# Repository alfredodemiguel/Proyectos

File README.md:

Recopilación de proyectos que realizo, por mero divertimento.
Este repositorio alberga proyectos, de dispositivos, con todo su software asociado y otros que son simples aplicaciones en Java o app moviles en React Native.

Dentro de cada proyecto hay una descripción mas detallada, de su función.

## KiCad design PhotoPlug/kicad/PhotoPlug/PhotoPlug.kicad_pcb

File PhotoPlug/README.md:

El proyecto consiste en la fabricación de un artefacto, que permite tomar fotografiás, y controlar una salida de luz.

De esta forma, podemos ver remotamente como se está desarrollando una impresión 3D, y si es necesario quitar la alimentación a la impresora.

El artefacto se puede controlar desde una red wifi propia, (que también se usa para la configuración inicial), o desde una web alojada en un servidor que está en un contenedor Docker alojado en Heroku, al igueal que un servidor API-REST.

El proyecto está separado por carpetas: el diseño de la placa base, el diseño de la caja para imprimir en 3D, la programación de la ESP32-CAM, la programación de la web, la programación del servidor API-REST, y la programación de la app movil android.

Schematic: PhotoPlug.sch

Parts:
C1, C2: CP1_Small; CP_Radial_D6.3mm_P2.50mm
F1, F2: Fuse; MiFusible
H1, H2, H3, H4: MountingHole; MountingHole_3.5mm
IC1: ESP32-CAM; ESP32CAM; Manufacturer_Part_Number ESP32-CAM
J1, J5: Screw_Terminal_01x02; Altech_AK300_1x02_P5.00mm_45-Degree
J2: Screw_Terminal_01x03; Altech_AK300_1x03_P5.00mm_45-Degree
J3: Screw_Terminal_01x02; Altech_AK300_1x03_P5.00mm_45-Degree
J4: Conn_01x08_MountingPin; PinSocket_1x08_P1.00mm_Vertical_SMD_Pin1Left
J6, J7, J8: Conn_01x02_MountingPin; PinHeader_1x02_P1.00mm_Vertical
K1: SRD-05VDC-SL-C; SRD; Manufacturer_Part_Number SRD-05VDC-SL-C
R1, R2, R3: R; R_Axial_DIN0204_L3.6mm_D1.6mm_P2.54mm_Vertical
RV1: Varistor; RV_Disc_D12mm_W4.8mm_P7.5mm
U1: Transformador100v-240v_5V_0.6A; Transformador Tenstar Robot

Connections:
+1V5: C1.1, C2.1, F2.1
+5V: IC1.8 (5V), J4.4, J4.5
GND: C1.2, C2.2, IC1.16 (GND_3), J4.1, J4.2, J4.3, J6.1, J7.1, J8.1, K1.3, U1.3
unnamed: F1.1, J2.2
unnamed: F1.2, K1.1, RV1.2, U1.0
unnamed: F2.2, U1.2
unnamed: IC1.1 (IO4), J4.6
unnamed: IC1.2 (IO2), J4.7
unnamed: IC1.3 (IO14), J4.8
unnamed: IC1.4 (IO15), R1.2, R2.2, R3.2
unnamed: IC1.6 (IO12), K1.2
unnamed: J1.1, J2.3, J3.2
unnamed: J1.2, J3.1, J5.1, RV1.1, U1.1
unnamed: J2.1, J5.2, K1.4
unnamed: J6.2, R3.1
unnamed: J7.2, R1.1
unnamed: J8.2, R2.1

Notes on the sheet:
Interruptor de tres posiciones
Entrada
Salida
PhotoPlug
Led_Encendido

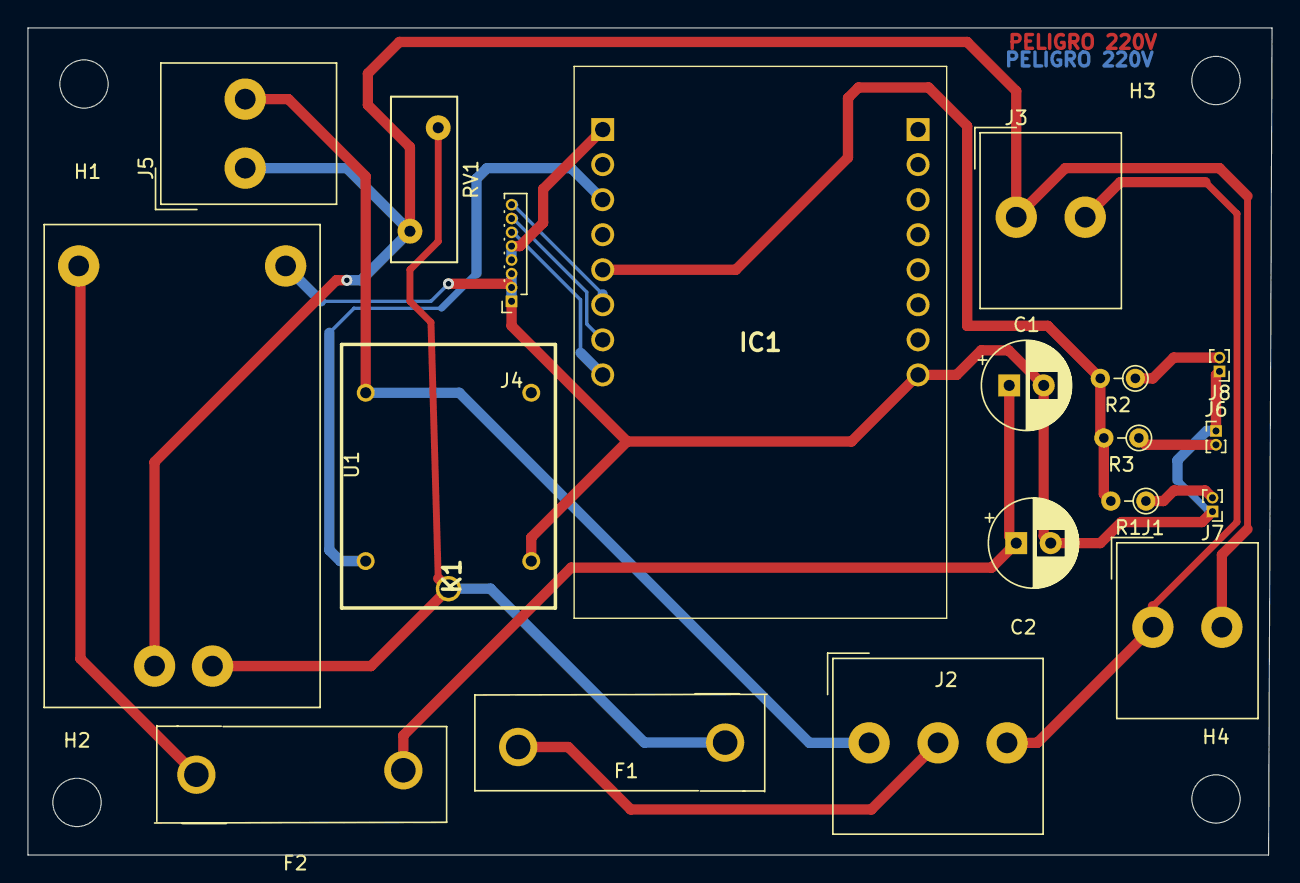
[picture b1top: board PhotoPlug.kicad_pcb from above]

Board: 2 copper layers, 90.2 x 59.9 mm, 23 parts (0 on the bottom side), 17 nets.

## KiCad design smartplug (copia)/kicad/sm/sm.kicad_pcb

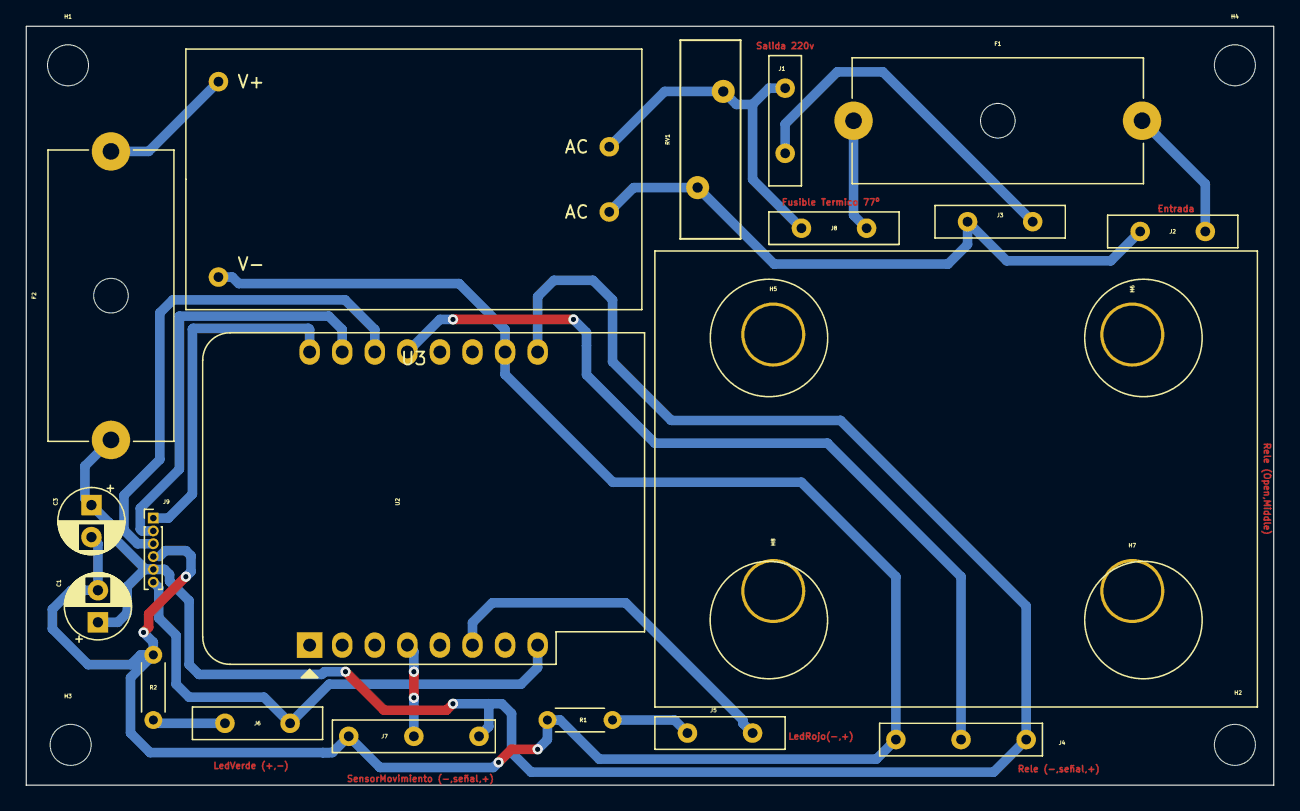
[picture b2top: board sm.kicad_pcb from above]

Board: 2 copper layers, 97.3 x 59.2 mm, 27 parts (0 on the bottom side), 17 nets.

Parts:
C1: Capacitor 22uF; CP_Radial_D5.0mm_P2.50mm
C3: Capacitor 10uF; CP_Radial_D5.0mm_P2.50mm
F1: Portafusible para fusible 5x20mm (Slow Blow 200mA); Fuseholder_Cylinder-5x20mm_Schurter_0031_8201_Horizontal_Op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
F2: Portafusible para fusible 5x20mm (Quick Blow 630m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; Fuseholder_Cylinder-5x20mm_Schurter_0031_8201_Horizontal_Op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
H1, H2, H3, H4, H5, H6, H7, H8: MountingHole; MountingHole_3.2mm_M3_DIN965
J1, J2, J3, J5, J6, J8: Screw_Terminal_01x02; Terminal_Tornillo_2
J4, J7: Screw_Terminal_01x03; Terminal_Tornillo_3
J9: Conn_01x06_Male; PinHeader_1x06_P1.00mm_Vertical
R1, R2: Resistencia 200 ohms; R_Axial_DIN0204_L3.6mm_D1.6mm_P5.08mm_Horizontal
RV1: Varistor 300 v 14d471k; RV_Disc_D15.5mm_W4.7mm_P7.5mm
U1: RELE QC3F-05VDC (10A 125-220 - 10A 30VDC); Rele_5vDC
U2: ESP8266 ESP-12F; ESP8266_ESP-12F3
U3: Transformador100v-240v_5V_0.6A; Transformador220v-5v

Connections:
+3V3: J6.1, J9.6, U2.8
+5V: C1.1, C3.1, F2.1, J4.3, J7.3, J9.5, U2.16
/Linea1: F1.2, J2.1
/Linea2: J2.2, J3.2, RV1.2, U3.1
GND: C1.2, C3.2, J4.1, J7.1, J9.4, R1.2, R2.2, U2.15, U3.2
unnamed: F1.1, J8.2
unnamed: F2.2, U3.3
unnamed: J1.1, J8.1, RV1.1, U3.0
unnamed: J1.2, J3.1
unnamed: J4.2, U2.12
unnamed: J5.1, U2.6
unnamed: J5.2, R1.1
unnamed: J6.2, R2.1
unnamed: J7.2, U2.4
unnamed: J9.1, U2.9
unnamed: J9.2, U2.10
unnamed: J9.3, U2.11

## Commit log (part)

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2020-03-04 organizacion
2020-03-22 Linux
2020-03-30 callbacks
2020-04-02 cambio pag
2020-04-03 Optimizar api
2020-04-11 API ok
2020-05-03 freecad
2020-05-06 Placa mas pequeña
2020-05-18 web arduino
2020-05-26 email
2020-05-30 Antes refactorizar
2020-06-04 Antes email
2020-06-17 Finalizando arduino
2020-06-21 Programa arduino
2020-07-05 Paso array
2020-07-10 web a medias
2020-07-11 web funcionando
2020-07-19 Bump lodash from 4.17.15 to 4.17.19 in /smartplug/system
    Bumps [lodash](https://github.com/lodash/lodash) from 4.17.15 to 4.17.19.
    - [Release notes](https://github.com/lodash/lodash/releases)
    - [Commits](https://github.com/lodash/lodash/compare/4.17.15...4.17.19)
2020-07-21 Web 1.0
2020-09-08 Integración con get
2020-09-15 FotoString
2020-10-11 fusion
2020-10-17 Paso a SD
2020-10-25 Comportamiento
2020-10-26 Hardware y web
2021-01-02 CajaLimpia
2021-01-05 Arduino revisado
2021-01-10 Bump dot-prop from 4.2.0 to 4.2.1 in /PhotoPlug/system
    Bumps [dot-prop](https://github.com/sindresorhus/dot-prop) from 4.2.0 to 4.2.1.
    - [Release notes](https://github.com/sindresorhus/dot-prop/releases)
    - [Commits](https://github.com/sindresorhus/dot-prop/compare/v4.2.0...v4.2.1)
2021-01-10 Bump ini from 1.3.5 to 1.3.8 in /PhotoPlug/system
    Bumps [ini](https://github.com/isaacs/ini) from 1.3.5 to 1.3.8.
    - [Release notes](https://github.com/isaacs/ini/releases)
    - [Commits](https://github.com/isaacs/ini/compare/v1.3.5...v1.3.8)
2021-01-19 AntesRefactorinWeb
2021-01-22 Bump dot-prop from 4.2.0 to 4.2.1 in /PhotoPlug/API
    Bumps [dot-prop](https://github.com/sindresorhus/dot-prop) from 4.2.0 to 4.2.1.
    - [Release notes](https://github.com/sindresorhus/dot-prop/releases)
    - [Commits](https://github.com/sindresorhus/dot-prop/compare/v4.2.0...v4.2.1)
2021-01-22 Bump lodash from 4.17.15 to 4.17.20 in /PhotoPlug/API
    Bumps [lodash](https://github.com/lodash/lodash) from 4.17.15 to 4.17.20.
    - [Release notes](https://github.com/lodash/lodash/releases)
    - [Commits](https://github.com/lodash/lodash/compare/4.17.15...4.17.20)
2021-01-22 Bump ini from 1.3.5 to 1.3.8 in /smartplug/system
    Bumps [ini](https://github.com/isaacs/ini) from 1.3.5 to 1.3.8.
    - [Release notes](https://github.com/isaacs/ini/releases)
    - [Commits](https://github.com/isaacs/ini/compare/v1.3.5...v1.3.8)
2021-01-22 Bump ini from 1.3.5 to 1.3.8 in /PhotoPlug/API
    Bumps [ini](https://github.com/isaacs/ini) from 1.3.5 to 1.3.8.
    - [Release notes](https://github.com/isaacs/ini/releases)
    - [Commits](https://github.com/isaacs/ini/compare/v1.3.5...v1.3.8)
2021-01-22 Bump axios from 0.19.2 to 0.21.1 in /PhotoPlug/webCamera/web
    Bumps [axios](https://github.com/axios/axios) from 0.19.2 to 0.21.1.
    - [Release notes](https://github.com/axios/axios/releases)
    - [Changelog](https://github.com/axios/axios/blob/v0.21.1/CHANGELOG.md)
    - [Commits](https://github.com/axios/axios/compare/v0.19.2...v0.21.1)
2021-01-24 PhotoPlug
2021-02-06 Botones app movil
2021-03-22 imagenes
2021-04-09 versionNode
2021-04-11 media web
2021-05-08 Bump ua-parser-js from 0.7.23 to 0.7.28 in /PhotoPlug/AppMovil/PhotoPlug
    Bumps [ua-parser-js](https://github.com/faisalman/ua-parser-js) from 0.7.23 to 0.7.28.
    - [Release notes](https://github.com/faisalman/ua-parser-js/releases)
    - [Commits](https://github.com/faisalman/ua-parser-js/compare/0.7.23...0.7.28)
2021-05-11 Bump hosted-git-info in /PhotoPlug/AppMovil/PhotoPlug
    Bumps [hosted-git-info](https://github.com/npm/hosted-git-info) from 2.8.8 to 2.8.9.
    - [Release notes](https://github.com/npm/hosted-git-info/releases)
    - [Changelog](https://github.com/npm/hosted-git-info/blob/v2.8.9/CHANGELOG.md)
    - [Commits](https://github.com/npm/hosted-git-info/compare/v2.8.8...v2.8.9)
2021-05-12 Bump lodash from 4.17.15 to 4.17.21 in /PhotoPlug/API
    Bumps [lodash](https://github.com/lodash/lodash) from 4.17.15 to 4.17.21.
    - [Release notes](https://github.com/lodash/lodash/releases)
    - [Commits](https://github.com/lodash/lodash/compare/4.17.15...4.17.21)
2021-06-12 Bump glob-parent from 5.1.1 to 5.1.2 in /PhotoPlug/AppMovil/PhotoPlug
    Bumps [glob-parent](https://github.com/gulpjs/glob-parent) from 5.1.1 to 5.1.2.
    - [Release notes](https://github.com/gulpjs/glob-parent/releases)
    - [Changelog](https://github.com/gulpjs/glob-parent/blob/main/CHANGELOG.md)
    - [Commits](https://github.com/gulpjs/glob-parent/compare/v5.1.1...v5.1.2)
    ---
    updated-dependencies:
2021-07-09 get funcionando
2021-07-17 antes try catch
2021-07-19 API sin test
2021-07-31 Test Inicio
2021-08-13 Bump path-parse from 1.0.6 to 1.0.7 in /PhotoPlug/AppMovil/PhotoPlug
    Bumps [path-parse](https://github.com/jbgutierrez/path-parse) from 1.0.6 to 1.0.7.
    - [Release notes](https://github.com/jbgutierrez/path-parse/releases)
    - [Commits](https://github.com/jbgutierrez/path-parse/commits/v1.0.7)
    ---
    updated-dependencies:
    - dependency-name: path-parse
2022-02-11 Bump pathval from 1.1.0 to 1.1.1 in /PhotoPlug/API
    Bumps [pathval](https://github.com/chaijs/pathval) from 1.1.0 to 1.1.1.
    - [Release notes](https://github.com/chaijs/pathval/releases)
    - [Changelog](https://github.com/chaijs/pathval/blob/master/CHANGELOG.md)
    - [Commits](https://github.com/chaijs/pathval/compare/v1.1.0...v1.1.1)
    ---
    updated-dependencies:
2022-02-14 Bump follow-redirects from 1.14.1 to 1.14.8 in /ApiSql
    Bumps [follow-redirects](https://github.com/follow-redirects/follow-redirects) from 1.14.1 to 1.14.8.
    - [Release notes](https://github.com/follow-redirects/follow-redirects/releases)
    - [Commits](https://github.com/follow-redirects/follow-redirects/compare/v1.14.1...v1.14.8)
    ---
    updated-dependencies:
    - dependency-name: follow-redirects
2022-03-29 Bump minimist from 1.2.5 to 1.2.6 in /PhotoPlug/AppMovil/PhotoPlug
    Bumps [minimist](https://github.com/substack/minimist) from 1.2.5 to 1.2.6.
    - [Release notes](https://github.com/substack/minimist/releases)
    - [Commits](https://github.com/substack/minimist/compare/1.2.5...1.2.6)
    ---
    updated-dependencies:
    - dependency-name: minimist
2022-03-30 Bump minimist from 1.2.5 to 1.2.6 in /ApiSql
    Bumps [minimist](https://github.com/substack/minimist) from 1.2.5 to 1.2.6.
    - [Release notes](https://github.com/substack/minimist/releases)
    - [Commits](https://github.com/substack/minimist/compare/1.2.5...1.2.6)
    ---
    updated-dependencies:
    - dependency-name: minimist
2022-06-02 Bump simple-plist from 1.1.1 to 1.3.1 in /PhotoPlug/AppMovil/PhotoPlug
    Bumps [simple-plist](https://github.com/wollardj/simple-plist) from 1.1.1 to 1.3.1.
    - [Release notes](https://github.com/wollardj/simple-plist/releases)
    - [Commits](https://github.com/wollardj/simple-plist/compare/v1.1.1...v1.3.1)
    ---
    updated-dependencies:
    - dependency-name: simple-plist
2022-06-22 Bump async from 3.2.0 to 3.2.4 in /ApiSql
    Bumps [async](https://github.com/caolan/async) from 3.2.0 to 3.2.4.
    - [Release notes](https://github.com/caolan/async/releases)
    - [Changelog](https://github.com/caolan/async/blob/master/CHANGELOG.md)
    - [Commits](https://github.com/caolan/async/compare/v3.2.0...v3.2.4)
    ---
    updated-dependencies:
2022-11-10 Bump minimatch and mocha in /PhotoPlug/API
    Bumps [minimatch](https://github.com/isaacs/minimatch) to 3.1.2 and updates ancestor dependency [mocha](https://github.com/mochajs/mocha). These dependencies need to be updated together.
    Updates `minimatch` from 3.0.4 to 3.1.2
    - [Release notes](https://github.com/isaacs/minimatch/releases)
    - [Commits](https://github.com/isaacs/minimatch/compare/v3.0.4...v3.1.2)
    Updates `mocha` from 6.2.2 to 10.1.0
    - [Release notes](https://github.com/mochajs/mocha/releases)
2022-11-10 Bump minimatch from 3.0.4 to 3.1.2 in /PhotoPlug/AppMovil/PhotoPlug
    Bumps [minimatch](https://github.com/isaacs/minimatch) from 3.0.4 to 3.1.2.
    - [Release notes](https://github.com/isaacs/minimatch/releases)
    - [Commits](https://github.com/isaacs/minimatch/compare/v3.0.4...v3.1.2)
    ---
    updated-dependencies:
    - dependency-name: minimatch
2022-12-07 Bump decode-uri-component from 0.2.0 to 0.2.2 in /PhotoPlug/API
    Bumps [decode-uri-component](https://github.com/SamVerschueren/decode-uri-component) from 0.2.0 to 0.2.2.
    - [Release notes](https://github.com/SamVerschueren/decode-uri-component/releases)
    - [Commits](https://github.com/SamVerschueren/decode-uri-component/compare/v0.2.0...v0.2.2)
    ---
    updated-dependencies:
    - dependency-name: decode-uri-component
2022-12-07 Bump decode-uri-component in /PhotoPlug/AppMovil/PhotoPlug
    Bumps [decode-uri-component](https://github.com/SamVerschueren/decode-uri-component) from 0.2.0 to 0.2.2.
    - [Release notes](https://github.com/SamVerschueren/decode-uri-component/releases)
    - [Commits](https://github.com/SamVerschueren/decode-uri-component/compare/v0.2.0...v0.2.2)
    ---
    updated-dependencies:
    - dependency-name: decode-uri-component
2022-12-08 Bump qs and express in /PersonalWeb
    Bumps [qs](https://github.com/ljharb/qs) to 6.11.0 and updates ancestor dependency [express](https://github.com/expressjs/express). These dependencies need to be updated together.
    Updates `qs` from 6.7.0 to 6.11.0
    - [Release notes](https://github.com/ljharb/qs/releases)
    - [Changelog](https://github.com/ljharb/qs/blob/main/CHANGELOG.md)
    - [Commits](https://github.com/ljharb/qs/compare/v6.7.0...v6.11.0)
    Updates `express` from 4.17.1 to 4.18.2
2022-12-12 Bump qs from 6.5.2 to 6.5.3 in /PhotoPlug/AppMovil/PhotoPlug
    Bumps [qs](https://github.com/ljharb/qs) from 6.5.2 to 6.5.3.
    - [Release notes](https://github.com/ljharb/qs/releases)
    - [Changelog](https://github.com/ljharb/qs/blob/main/CHANGELOG.md)
    - [Commits](https://github.com/ljharb/qs/compare/v6.5.2...v6.5.3)
    ---
    updated-dependencies:
2022-12-13 Bump express from 4.17.1 to 4.17.3 in /PhotoPlug/webCamera/system
    Bumps [express](https://github.com/expressjs/express) from 4.17.1 to 4.17.3.
    - [Release notes](https://github.com/expressjs/express/releases)
    - [Changelog](https://github.com/expressjs/express/blob/master/History.md)
    - [Commits](https://github.com/expressjs/express/compare/4.17.1...4.17.3)
    ---
    updated-dependencies:
2022-12-14 Bump express from 4.17.1 to 4.17.3 in /PersonalWeb
    Bumps [express](https://github.com/expressjs/express) from 4.17.1 to 4.17.3.
    - [Release notes](https://github.com/expressjs/express/releases)
    - [Changelog](https://github.com/expressjs/express/blob/master/History.md)
    - [Commits](https://github.com/expressjs/express/compare/4.17.1...4.17.3)
    ---
    updated-dependencies:
2022-12-14 Bump express from 4.17.1 to 4.17.3 in /ApiSql
    Bumps [express](https://github.com/expressjs/express) from 4.17.1 to 4.17.3.
    - [Release notes](https://github.com/expressjs/express/releases)
    - [Changelog](https://github.com/expressjs/express/blob/master/History.md)
    - [Commits](https://github.com/expressjs/express/compare/4.17.1...4.17.3)
    ---
    updated-dependencies:
2023-01-06 Bump json5 from 2.1.3 to 2.2.3 in /PhotoPlug/AppMovil/PhotoPlug
    Bumps [json5](https://github.com/json5/json5) from 2.1.3 to 2.2.3.
    - [Release notes](https://github.com/json5/json5/releases)
    - [Changelog](https://github.com/json5/json5/blob/main/CHANGELOG.md)
    - [Commits](https://github.com/json5/json5/compare/v2.1.3...v2.2.3)
    ---
    updated-dependencies:
